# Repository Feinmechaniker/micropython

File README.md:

# MicroPython
The MicroPython project

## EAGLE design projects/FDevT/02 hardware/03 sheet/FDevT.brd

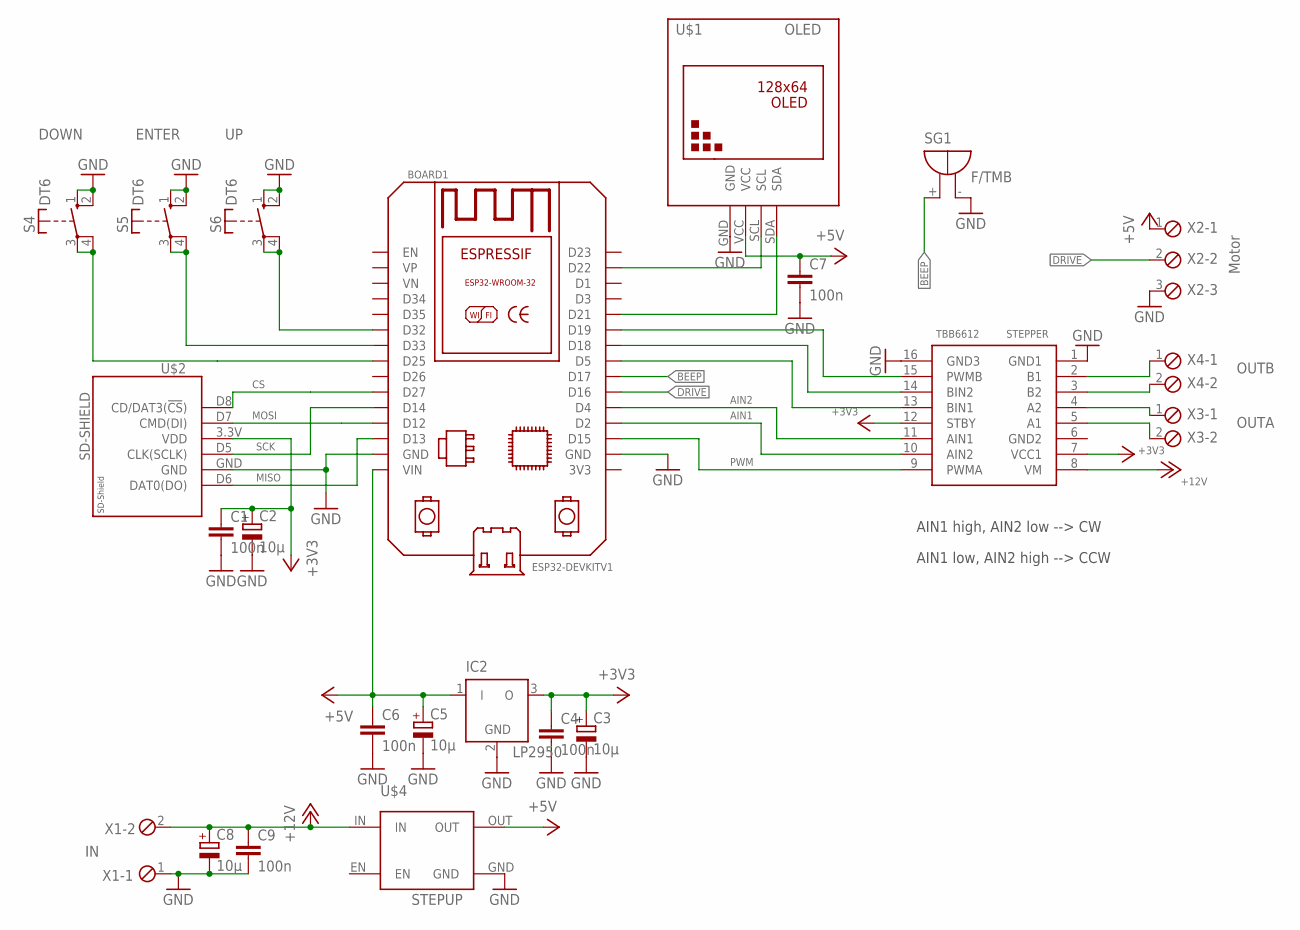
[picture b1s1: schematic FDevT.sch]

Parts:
BOARD1: ESP32DEVKITV1; ESP32-DEVKITV1
C1, C4, C6, C7, C9: 100n; C0805
C2, C3, C5, C8: 10µ; SMC_B
IC2: LP2950; DPACK
S4, S5, S6: DT6
SG1: F/TMB
STEPPER: TBB6612; DRIVER
U$1: OLED; SIP
U$2: SD-SHIELD; SD_SHIELD
U$4: STEPUP
X1: IN; 2POL254
X2: Motor; 3POL254
X3: OUTA; 2POL254
X4: OUTB; 2POL254

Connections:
+3V3: C1.1, C2.+, C3.+, C4.1, IC2.3 (O), STEPPER.7 (VCC1), STEPPER.12 (STBY), U$2.3.3V (VDD)
+5V: BOARD1.VIN, C5.+, C6.1, C7.1, IC2.1 (I), U$1.VCC, U$4.OUT, X2.1
+12V: C8.+, C9.1, STEPPER.8 (VM), U$4.IN, X1.2
AIN1: BOARD1.D2, STEPPER.10 (AIN2)
AIN2: BOARD1.D4, STEPPER.11 (AIN1)
BEEP: BOARD1.D17, SG1.+
CS: BOARD1.D27, U$2.D8 (CD/DAT3(!CS!))
DOWN: BOARD1.D25, S4.3, S4.4
DRIVE: BOARD1.D16, X2.2
ENTER: BOARD1.D33, S5.3, S5.4
GND: BOARD1.GND, BOARD1.GND@1 (GND), C1.2, C2.-, C3.-, C4.2, C5.-, C6.2, C7.2, C8.-, C9.2, IC2.2 (GND), S4.1 (S), S4.2 (S), S5.1 (S), S5.2 (S), S6.1 (S), S6.2 (S), SG1.-, STEPPER.1 (GND1), STEPPER.16 (GND3), U$1.GND, U$2.GND, U$4.GND, X1.1, X2.3
MISO: BOARD1.D13, U$2.D6 (DAT0(DO))
MOSI: BOARD1.D12, U$2.D7 (CMD(DI))
unnamed: BOARD1.D22, U$1.SCL
unnamed: BOARD1.D21, U$1.SDA
unnamed: STEPPER.5 (A1), X3.2
unnamed: STEPPER.4 (A2), X3.1
unnamed: BOARD1.D5, STEPPER.13 (BIN1)
unnamed: BOARD1.D18, STEPPER.14 (BIN2)
unnamed: BOARD1.D19, STEPPER.15 (PWMB)
unnamed: STEPPER.3 (B2), X4.2
unnamed: STEPPER.2 (B1), X4.1
PWM: BOARD1.D15, STEPPER.9 (PWMA)
SCK: BOARD1.D14, U$2.D5 (CLK(SCLK))
UP: BOARD1.D32, S6.3, S6.4

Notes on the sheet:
AIN1 high, AIN2 low --> CW
AIN1 low, AIN2 high --> CCW

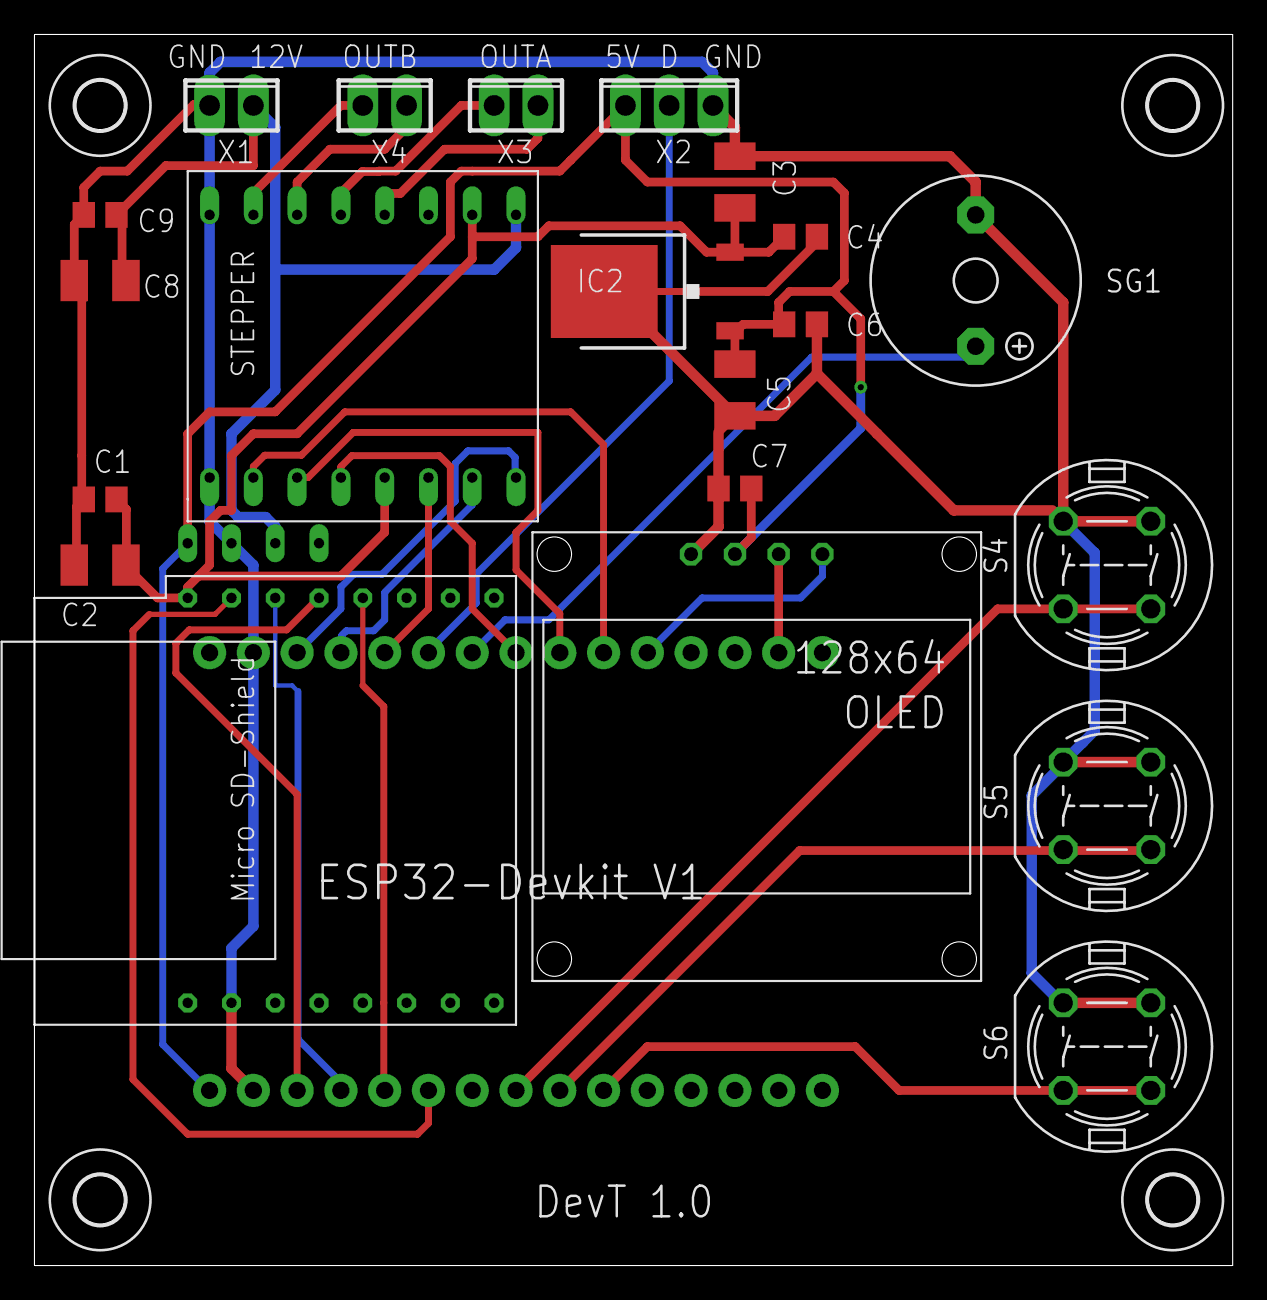
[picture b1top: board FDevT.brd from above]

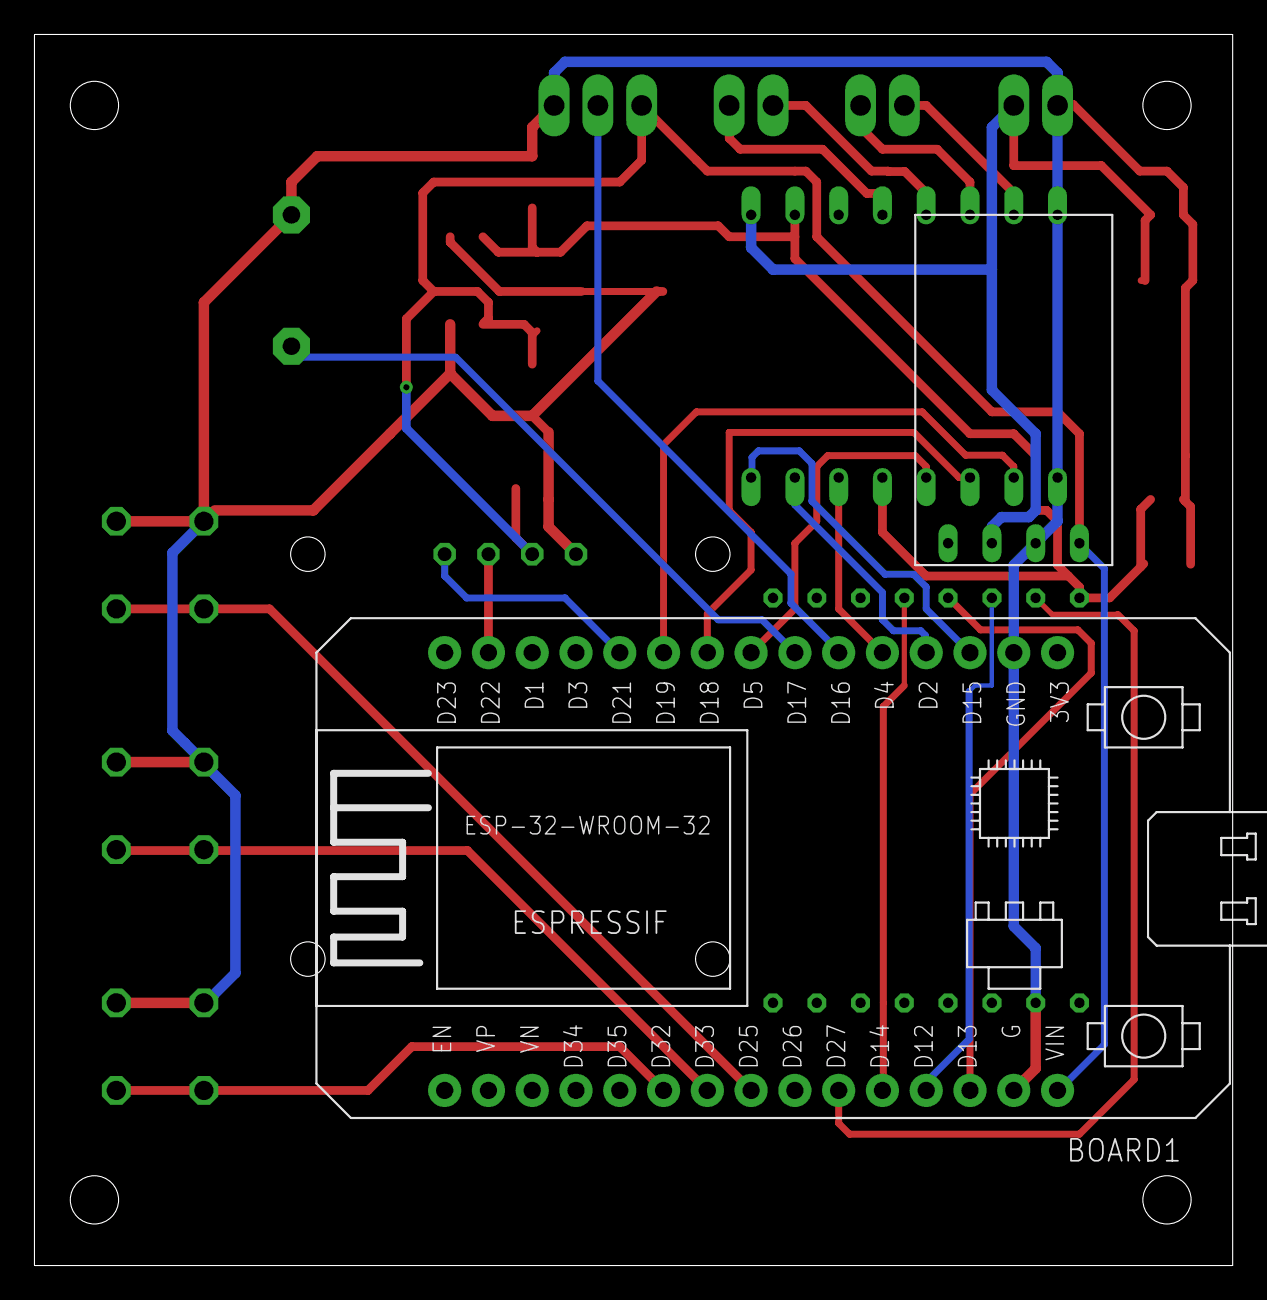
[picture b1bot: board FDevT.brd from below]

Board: 2 copper layers, 69.5 x 71.4 mm, 27 parts (2 on the bottom side), 25 nets.

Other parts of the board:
U$5, U$6, U$7, U$8: 2,8

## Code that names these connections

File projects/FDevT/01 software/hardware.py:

# -*- coding: utf-8 -*-
"""
Created on Wed Nov 29 08:24:08 2023

@author: Grabow
"""
__version__ = '1.0'
__author__ = 'Joe Grabow'

from machine import Pin

# Debugging
debug = True

# SD-Card
MOSI = Pin(12)
MISO = Pin(13)
SCK = Pin(14)
CS = Pin(27)

SD_CARD_PATH = '/sd'
TARGET_FILE = 'default.json'

# OLED
SDA = 21
SCL = 22
OLED_WIDTH = 128 
OLED_HEIGHT = 64

# Motor
PWM_FREQUENCY = 100
PWM_PIN = 15  # GPIO-Pin for Motor 1 Drive (PWMA)
MOTOR_PIN_A1 = 2  # GPIO-Pin H-Bridge Change (AIN1)
MOTOR_PIN_A2 = 4  # GPIO-Pin H-Bridge Change (AIN2)
MOTOR_2_PIN = 16  # 2nd Motor
# Beep
BEEP_PIN = 17

# Buttons
BUTTON_PINS = [32, 33, 25]  # Pin 32 is UP, Pin 33 is ENTER, Pin 25 is DOWN

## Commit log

2023-11-24 example image
2023-11-24 ssd1306 code
2023-11-24 example figure
2023-11-25 readme
2023-11-29 first version
2023-11-29 state-machine for process
2023-11-30 Version 1.0
2023-12-04 new version
2024-03-10 final Version
2025-01-23 overview picture
